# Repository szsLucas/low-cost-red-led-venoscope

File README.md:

# Portable Low-Cost Red-LED Venoscope

**An academic biomedical-engineering prototype for qualitative visualization of superficial veins using visible red light.**

> **Research and education only.** This is not a certified medical device and must not be used to guide clinical venipuncture or make medical decisions. The reported observations are qualitative; the optical contrast values are theoretical predictions, not measurements.

[Read the full paper (PDF)](article/venoscope-paper.pdf) · [Português](README.pt-BR.md) · [Reproducibility checklist](docs/reproducibility-checklist.md)

## Prototype overview

The project investigates whether a compact ring of visible red LEDs can produce an observable difference between superficial venous structures and surrounding tissue. The reported prototype combines a **12-LED ring**, a central viewing aperture, a **3D-printed enclosure designed in Tinkercad**, a **manually etched copper PCB**, four 1.5 V batteries, an on/off switch, and a 1 kΩ potentiometer for brightness adjustment.

Unlike near-infrared vein finders, this implementation **does not use an NIR camera, digital image processing, or vein projection**. It relies on direct observation under reduced ambient illumination.

| Front view — paper Fig. 1 | LED-facing side — paper Fig. 2 |
|:--:|:--:|
|  |  |

*Images reproduced from the authors' manuscript. Editable KiCad files have now been supplied, but they have **not yet been verified** against the physical prototype.*

## Hardware specifications

| Property | Value / documentation status |
|---|---|
| Illumination | 12 visible red LEDs, 5 mm typical device assumed for calculations |
| LED peak wavelength | Approximately **630 nm, assumed**; exact LED part number and spectrum were not recorded |
| Supply | Four 1.5 V cells in series (**6 V nominal**) |
| User controls | On/off switch; 1 kΩ potentiometer wired as a rheostat |
| LED forward voltage in calculations | 2.2 V assumed |
| Current-limiting design | **220 Ω per LED**, in 12 parallel branches — **recommended reference topology, not an independently verified as-built schematic** |
| Nominal current | ~17.27 mA per LED; ~207 mA for 12 LEDs at the minimum rheostat resistance (theoretical) |
| Resistor dissipation | ~65.6 mW per branch; ¼ W rated resistors recommended |
| Potentiometer dissipation | Up to ~0.20 W predicted; ≥0.5 W rating recommended |
| Housing and board | Tinkercad enclosure / 3D printing; chemical etching of a copper board with FeCl₃ |
| Firmware | None — analog LED illumination and manual brightness adjustment |

**Important:** The paper recommends individual 220 Ω resistors but also states that the actual wiring, installed component values, and PCB traces should be checked with a multimeter. Subsequently supplied KiCad source files are now available in [`hardware/kicad/`](hardware/kicad/). They have **not been verified as the as-built circuit**; their components and topology differ from the paper's recommended nominal circuit. No verified fabrication files have been provided.

### Electrical principle

For a 6 V source and an assumed LED forward voltage of 2.2 V:

```text
I_LED ≈ (6.0 − 2.2) / 220 = 17.27 mA  [at RP = 0 Ω]
P_R   ≈ I_LED² × 220 = 65.6 mW

12 identical branches in parallel, each: 220 Ω + 1 red LED
S1 (on/off) and RP (1 kΩ rheostat) are common to the 12 branches.
```

*The diagram above **reconstructs the article's recommended nominal topology**. It is not a measured, traced, or validated reproduction of the assembled PCB.*

The common rheostat produces a nonlinear brightness response: the paper's model predicts ~15.5% of maximum brightness at 100 Ω, ~3.5% at 500 Ω, and ~1.8% at 1 kΩ. An appropriately designed MOSFET/PWM driver is a proposed future improvement, **not a feature of this prototype**.

### Editable KiCad design files — verification pending

- [KiCad schematic (`Venoscopio.kicad_sch`)](hardware/kicad/Venoscopio.kicad_sch)
- [KiCad PCB layout (`Venoscopio.kicad_pcb`)](hardware/kicad/Venoscopio.kicad_pcb)
- [Comparison of the KiCad files with the manuscript](docs/kicad-vs-paper.md)

**Important difference:** The supplied KiCad schematic contains **one resistor (`R1`) for 12 LEDs**, whereas the paper recommends **one separate 220 Ω resistor per LED**. The PCB file also references a **3×AAA battery holder** and **3 mm LED footprints**, while the manuscript describes a nominal 6 V supply and assumes a typical 5 mm LED for the calculations. Component values are not populated for `R1` or `RV1` in the CAD files. These are document discrepancies, **not verified measurements of the physical prototype**. Do not treat the files as production-ready; inspect the wiring and run KiCad ERC/DRC before fabrication.

### KiCad design screenshots

The following four previews were provided alongside the editable design files. They document the **submitted CAD views**, rather than independently verified photographs of the fabricated PCB.

| 3D rendering — component/LED side | 3D rendering — reverse side |
|:--:|:--:|
|  |  |

| PCB layout in KiCad | Electrical schematic in KiCad |
|:--:|:--:|
|  |  |

**Design status:** These images are informational previews, not ERC/DRC evidence or proof of fully routed nets. Before manufacturing, check all schematic connections and airwires, confirm the battery holder and current-limiting topology, and compare the CAD with the physical prototype. [Full verification notes](docs/kicad-vs-paper.md).

### Enclosure finish and protective mask (proposed final revision)

For the final enclosure, **black—preferably with a matte finish—is the recommended design color**. This choice is intended to reduce unwanted reflections from the red illumination near the viewing area and provide a more uniform external finish; it has **not yet been evaluated through comparative optical measurements**.

The final assembly should also incorporate an **opaque mechanical mask** positioned **between the enclosure surface and the PCB**. This insert would conceal the **LED solder joints and exposed connection points**, leaving the LED emitting surfaces and central observation aperture unobstructed. Its geometry, attachment method, and clearances should be defined alongside the enclosure CAD to ensure electrical isolation and ease of assembly.

Here, *mask* means a **physical protective/finishing insert**, **not** the PCB's solder-mask coating. The black finish and mechanical mask are **proposed improvements**, not features documented as implemented or tested in the current prototype.

## Optical model

The paper uses a simplified, effective-attenuation model to estimate the reduction in diffuse red light in superficial tissue and the additional absorption associated with venous blood.

| Estimated quantity | Theoretical value (illustrative conditions) |
|---|---:|
| Effective attenuation coefficient in skin, μ_eff | ~0.671 mm⁻¹ |
| Remaining diffuse light after 1.5 mm of skin-equivalent path | **~36.5% of I₀** |
| Predicted intensity for a path that also includes 1.5 mm of venous blood | **~8.3% of I₀** |
| Idealized vein-to-background contrast | **~77.3%** |

These predictions assume optical coefficients from the literature, anisotropy **g = 0.8**, and illustrative skin and vein optical paths. **77.3% is not an experimentally established contrast, accuracy, or success rate.** The simplified calculation does not fully model 3D light transport, round-trip paths, pigmentation, geometry, or multiple scattering.

The calculation and theoretical brightness curve can be reproduced from the paper's reported constants:

```bash
python -m pip install -r requirements.txt
python analysis/reproduce_models.py --output-dir analysis/generated
python -m unittest discover -s tests -v
```

This code reproduces **paper calculations only**; it does not control the physical device or process clinical images. See [analysis documentation](analysis/README.md).

## Qualitative observations

Under reduced ambient illumination and manually adjusted LED brightness, the article reports **darker, vessel-like trajectories** in forearm photographs.

| Forearm observation — paper Fig. 4 | Second observation — paper Fig. 5 |
|:--:|:--:|
|  |  |

**What the observations do not establish:** vessel localization accuracy, maximum visualization depth, sensitivity/specificity, improvements in cannulation, performance across skin types, or clinical safety. No calibrated imaging, irradiance measurements, optical phantom, or controlled clinical protocol were reported.

## Repository structure

```text
.
├── README.md / README.pt-BR.md     Project documentation (EN / PT-BR)
├── article/venoscope-paper.pdf     Original academic manuscript
├── assets/figures/                Figures extracted from the paper
├── hardware/
│   ├── schematic/                  CONCEPTUAL diagram (paper recommendation)
│   ├── kicad/                      Editable schematic, PCB and four CAD previews; not validated
│   ├── pcb/                        Manufacturing files and physical inspection pending
│   └── enclosure/                  Placeholder for STL / editable 3D design
├── analysis/                        Reproducible first-order analytical models
├── docs/
│   ├── bill-of-materials.csv       Reference values and verification flags
│   ├── experimental-protocol.md   Proposed future evaluation (not performed)
│   └── reproducibility-checklist.md
├── tests/                           Tests of the analytical model
└── LICENSE-NOTICE.md               Rights / permissions to confirm
```

## Reproducibility and next steps

The original paper documents the principle and preliminary qualitative results, but **it is not yet a complete build package**. Priority additions are:

1. **As-built electrical documentation:** clear images of both PCB faces; measured component values; continuity/netlist trace; an actual schematic and matching PCB CAD/Gerbers.
2. **Manufacturing files:** editable Tinkercad export/source link if shareable, STL/STEP, dimensions, tolerances, assembly photos, fasteners, battery compartment details, and the proposed matte-black finish and mechanical mask that conceals LED solder joints.
3. **Measured performance:** battery voltage and current at several settings, per-branch current, potentiometer temperature, LED temperature, operating time, and optical irradiance.
4. **Controlled imaging data:** fixed distance, exposure, ambient light, and documented test geometry; compare contrast against a non-illuminated baseline and, if available, a tissue-mimicking phantom.
5. **Future architecture:** consider PWM dimming and individually limited LED currents; evaluate different wavelengths with appropriate optical sensing and safety review.

See the [detailed checklist](docs/reproducibility-checklist.md) and [proposed protocol](docs/experimental-protocol.md). Items in the future-work documents are **not claims of completed experiments**.

## Authors and attribution

- **Evellyn de Abreu** — [ORCID 0009-0009-8709-1542](https://orcid.org/0009-0009-8709-1542)
- **Lucas Silva Souza** — [ORCID 0009-0008-6328-7826](https://orcid.org/0009-0008-6328-7826)
- **Matheus Henrique Cruz** — [ORCID 0009-0001-3356-7199](https://orcid.org/0009-0001-3356-7199)

**Institution:** Faculty of Electrical Engineering, Federal University of Uberlândia (UFU), Brazil.

Please attribute the three authors when reusing the manuscript or derived materials. **No journal acceptance, peer-reviewed publication, project DOI, or license is claimed here.** Confirm publication and reuse permissions with all coauthors before making the repository public; see [LICENSE-NOTICE.md](LICENSE-NOTICE.md).

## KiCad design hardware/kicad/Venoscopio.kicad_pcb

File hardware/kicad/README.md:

# KiCad source — supplied design (unverified)

These files were provided by a project contributor and copied here **without modifying their internal content**:

- `Venoscopio.kicad_sch` — editable KiCad 10 schematic;
- `Venoscopio.kicad_pcb` — editable KiCad 10 PCB layout.

Both filenames were normalized to ASCII for convenient GitHub paths. They must be kept together with the same basename. You can open them individually in KiCad; no `.kicad_pro` file was supplied.

**Status:** They document a supplied design revision, not necessarily the assembled board. The documents have not been validated with ERC, DRC, multimeter measurements, or a hardware inspection. Read [`../../docs/kicad-vs-paper.md`](../../docs/kicad-vs-paper.md) before using them to fabricate anything.

Do not mistake the SVG under `../schematic/` for an export of this KiCad schematic; that SVG represents the recommended article topology.

## Visual previews provided with these sources

| Component-side 3D render | Reverse-side 3D render |
|:--:|:--:|
|  |  |

| PCB layout screenshot | Schematic screenshot |
|:--:|:--:|
|  |  |

These are screenshots of the **supplied CAD design**, not photographs or verified electrical/manufacturing outputs. The PCB editor screenshot may show incomplete routing; no ERC/DRC verification is claimed.

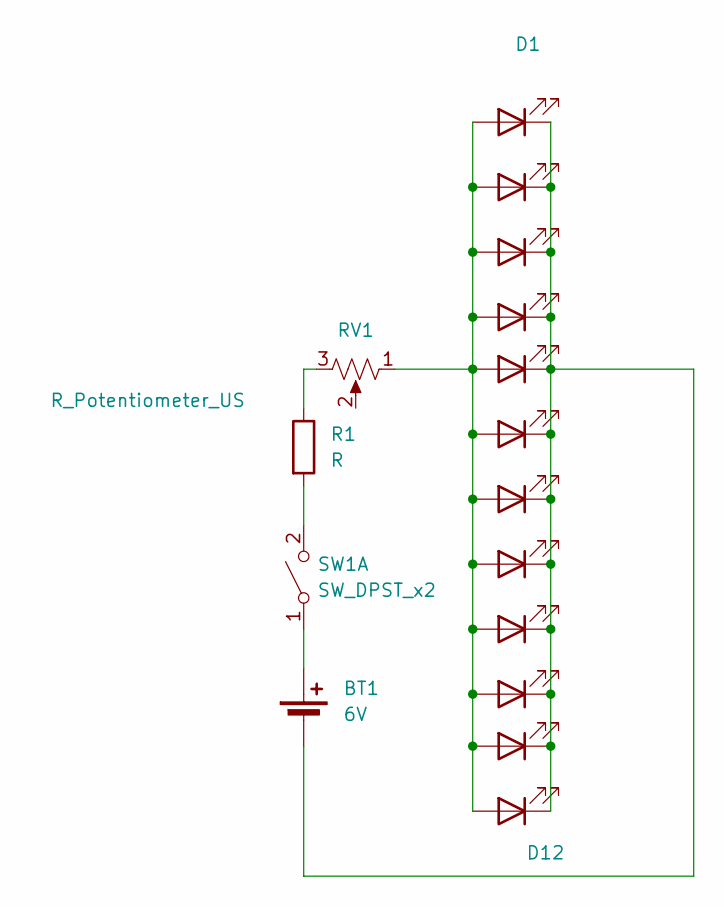
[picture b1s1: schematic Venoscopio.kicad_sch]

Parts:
BT1: 6V; BatteryHolder_Keystone_2479_3xAAA
D1, D2, D3, D4, D5, D6, D7, D8, D9, D10, D11, D12: LED; LED_D3.0mm_Clear
R1: R; R_Axial_DIN0204_L3.6mm_D1.6mm_P7.62mm_Horizontal
RV1: R_Potentiometer_US; Potentiometer_Omeg_PC16BU_Horizontal
SW1: SW_DPST_x2; SW_CK_JS202011AQN_DPDT_Angled

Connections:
unnamed: BT1.1 (+), SW1.1 (A)
unnamed: BT1.2 (-), D1.1 (K), D2.1 (K), D3.1 (K), D4.1 (K), D5.1 (K), D6.1 (K), D7.1 (K), D8.1 (K), D9.1 (K), D10.1 (K), D11.1 (K), D12.1 (K)
unnamed: D1.2 (A), D2.2 (A), D3.2 (A), D4.2 (A), D5.2 (A), D6.2 (A), D7.2 (A), D8.2 (A), D9.2 (A), D10.2 (A), D11.2 (A), D12.2 (A), RV1.1
unnamed: R1.1, RV1.3
unnamed: R1.2, SW1.2 (B)

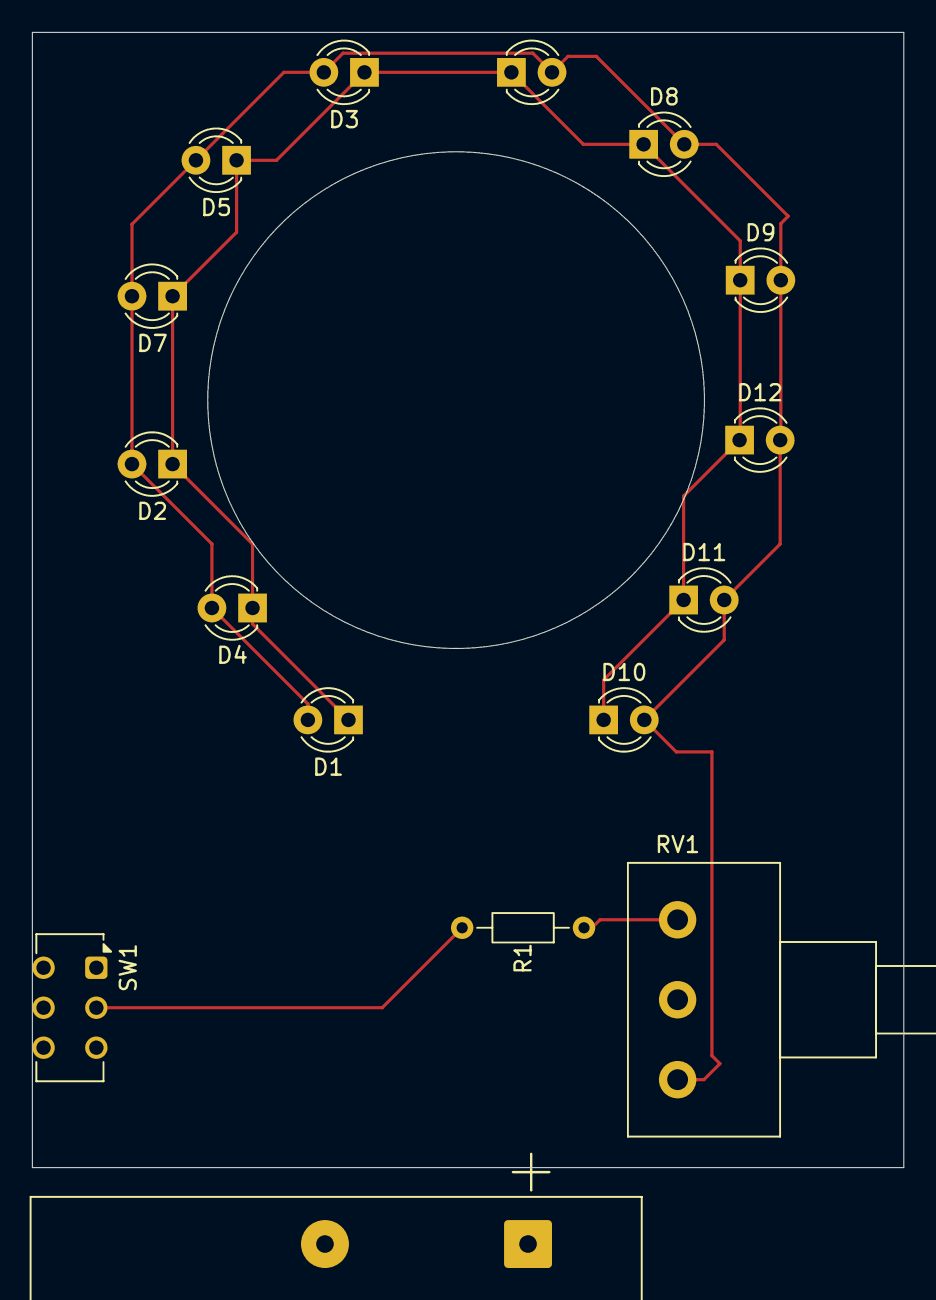
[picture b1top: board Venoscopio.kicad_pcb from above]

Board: 2 copper layers, 54.5 x 71.0 mm, 16 parts (0 on the bottom side), 5 nets.
